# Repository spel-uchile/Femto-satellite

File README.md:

# README #

Femto-satellite v3.211109

### Description ###

This is a low-cost satellite of less than 100 grams. The goal is to deploy two femto-satellites from a 3U CubeSat to validate a localization system based on TDOA and AOA.

### Current features ###

 * GPS localization
 * S band communication
 * 32-bit ARM Cortex M0+ microcontroller
 * Magnetometer PNI RM3100
 * Data logger using a microSD card
 
### To do ###

 * Update the software for the new hardware version
 * Program a low-power mode

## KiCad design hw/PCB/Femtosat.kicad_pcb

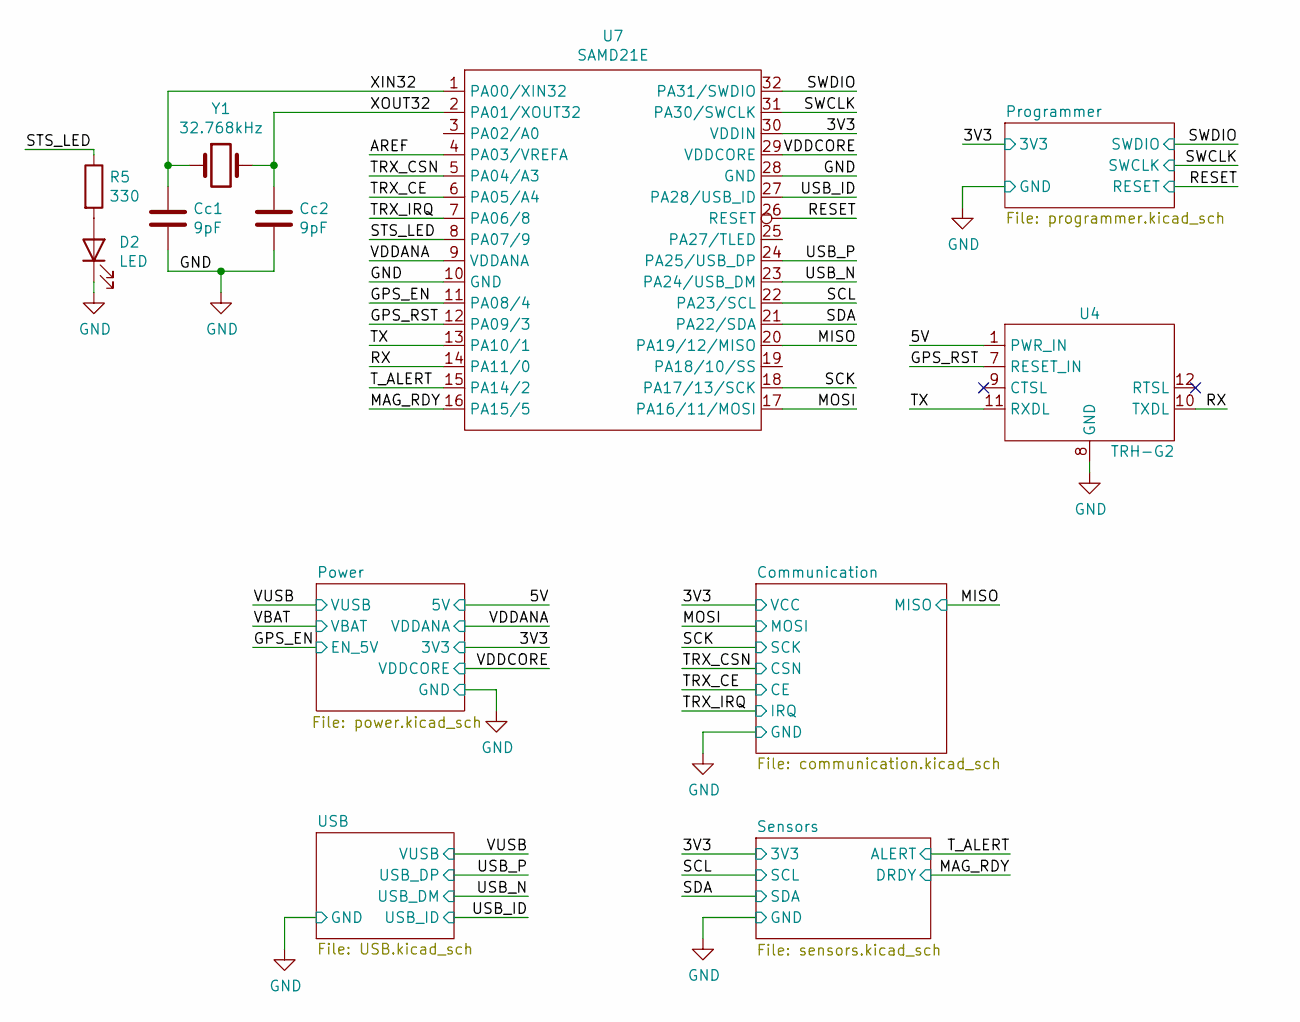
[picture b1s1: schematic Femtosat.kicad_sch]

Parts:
Cc1, Cc2: 9pF; C_0603_1608Metric_Pad1.05x0.95mm_HandSolder
D2: LED; LED_0805_2012Metric_Pad1.15x1.40mm_HandSolder
R5: 330; R_0603_1608Metric_Pad1.05x0.95mm_HandSolder
U4: TRH-G2; TRH-G2_extended
U7: SAMD21E; TQFP-32_7x7mm_P0.8mm
Y1: 32.768kHz; Crystal_SMD_EuroQuartz_EQ161-2Pin_3.2x1.5mm_HandSoldering

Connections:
+3V3: U7.30 (VDDIN); also elsewhere on the board
/5V: U4.1 (PWR_IN), U4.2 (PWR_IN); also elsewhere on the board
/AREF: U7.4 (PA03/VREFA)
/GPS_EN: U7.11 (PA08/4); also elsewhere on the board
/GPS_RST: U4.7 (RESET_IN), U7.12 (PA09/3)
/MAG_RDY: U7.16 (PA15/5); also elsewhere on the board
/MISO: U7.20 (PA19/12/MISO); also elsewhere on the board
/MOSI: U7.17 (PA16/11/MOSI); also elsewhere on the board
/RESET: U7.26 (RESET); also elsewhere on the board
/RX: U4.10 (TXDL), U7.14 (PA11/0)
/SCK: U7.18 (PA17/13/SCK); also elsewhere on the board
/SCL: U7.22 (PA23/SCL); also elsewhere on the board
/SDA: U7.21 (PA22/SDA); also elsewhere on the board
/STS_LED: R5.1, U7.8 (PA07/9)
/SWCLK: U7.31 (PA30/SWCLK); also elsewhere on the board
/SWDIO: U7.32 (PA31/SWDIO); also elsewhere on the board
/TRX_CE: U7.6 (PA05/A4); also elsewhere on the board
/TRX_CSN: U7.5 (PA04/A3); also elsewhere on the board
/TRX_IRQ: U7.7 (PA06/8); also elsewhere on the board
/TX: U4.11 (RXDL), U7.13 (PA10/1)
/T_ALERT: U7.15 (PA14/2); also elsewhere on the board
/USB_ID: U7.27 (PA28/USB_ID); also elsewhere on the board
/USB_N: U7.23 (PA24/USB_DM); also elsewhere on the board
/USB_P: U7.24 (PA25/USB_DP); also elsewhere on the board
/VDDANA: U7.9 (VDDANA); also elsewhere on the board
/VDDCORE: U7.29 (VDDCORE); also elsewhere on the board
/XIN32: Cc1.1, U7.1 (PA00/XIN32), Y1.1
/XOUT32: Cc2.1, U7.2 (PA01/XOUT32), Y1.2
GND: Cc1.2, Cc2.2, D2.1 (K), U4.3 (PGND), U4.4 (PGND), U4.5 (-), U4.6 (-), U4.8 (GND), U7.10 (GND), U7.28 (GND); also elsewhere on the board
unnamed: D2.2 (A), R5.2

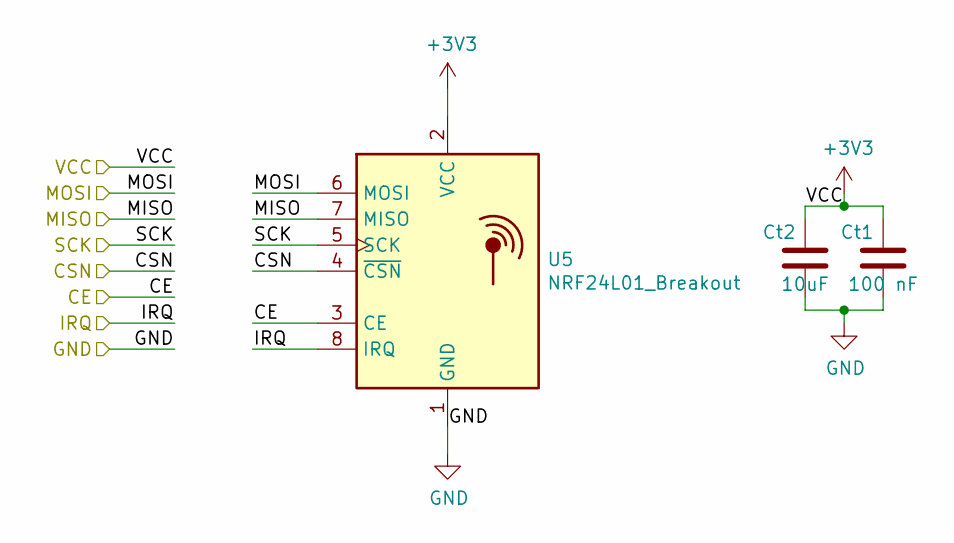
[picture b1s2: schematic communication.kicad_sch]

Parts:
Ct1: 100 nF; C_0603_1608Metric_Pad1.05x0.95mm_HandSolder
Ct2: 10uF; C_0603_1608Metric_Pad1.05x0.95mm_HandSolder
U5: NRF24L01_Breakout; nRF24L01_long

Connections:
+3V3: Ct1.2, Ct2.2, U5.2 (VCC); also elsewhere on the board
/MISO: U5.7 (MISO); also elsewhere on the board
/MOSI: U5.6 (MOSI); also elsewhere on the board
/SCK: U5.5 (SCK); also elsewhere on the board
/TRX_CE: U5.3 (CE); also elsewhere on the board
/TRX_CSN: U5.4 (~CSN); also elsewhere on the board
/TRX_IRQ: U5.8 (IRQ); also elsewhere on the board
GND: Ct1.1, Ct2.1, U5.1 (GND); also elsewhere on the board

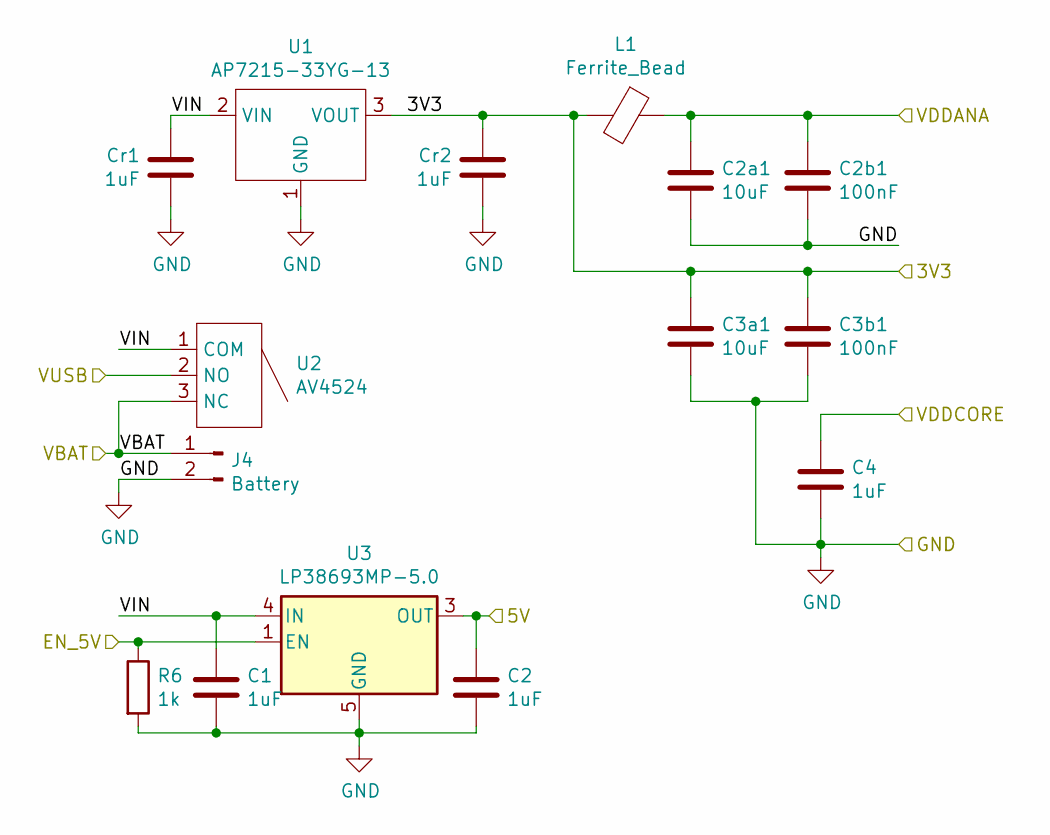
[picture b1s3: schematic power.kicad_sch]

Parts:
C1, C2, C4: 1uF; C_0603_1608Metric_Pad1.05x0.95mm_HandSolder
C2a1, C3a1: 10uF; C_0603_1608Metric_Pad1.05x0.95mm_HandSolder
C2b1, C3b1: 100nF; C_0603_1608Metric_Pad1.05x0.95mm_HandSolder
Cr1, Cr2: 1uF; C_0603_1608Metric_Pad1.05x0.95mm_HandSolder
J4: Battery; JST_PH_S2B-PH-K_1x02_P2.00mm_Horizontal
L1: Ferrite_Bead; L_0805_2012Metric_Pad1.15x1.40mm_HandSolder
R6: 1k; R_0603_1608Metric_Pad1.05x0.95mm_HandSolder
U1: AP7215-33YG-13; SOT-89-3
U2: AV4524
U3: LP38693MP-5.0; SOT-223-5

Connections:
+3V3: C3a1.1, C3b1.1, Cr2.1, L1.2, U1.3 (VOUT); also elsewhere on the board
/5V: C2.1, U3.3 (OUT); also elsewhere on the board
/GPS_EN: R6.1, U3.1 (EN); also elsewhere on the board
/Power/VIN: C1.1, Cr1.1, U1.2 (VIN), U2.1 (COM), U3.4 (IN)
/VBAT: J4.1, U2.3 (NC)
/VDDANA: C2a1.1, C2b1.1, L1.1; also elsewhere on the board
/VDDCORE: C4.1; also elsewhere on the board
/VUSB: U2.2 (NO); also elsewhere on the board
GND: C1.2, C2.2, C2a1.2, C2b1.2, C3a1.2, C3b1.2, C4.2, Cr1.2, Cr2.2, J4.2, R6.2, U1.1 (GND), U3.5 (GND); also elsewhere on the board

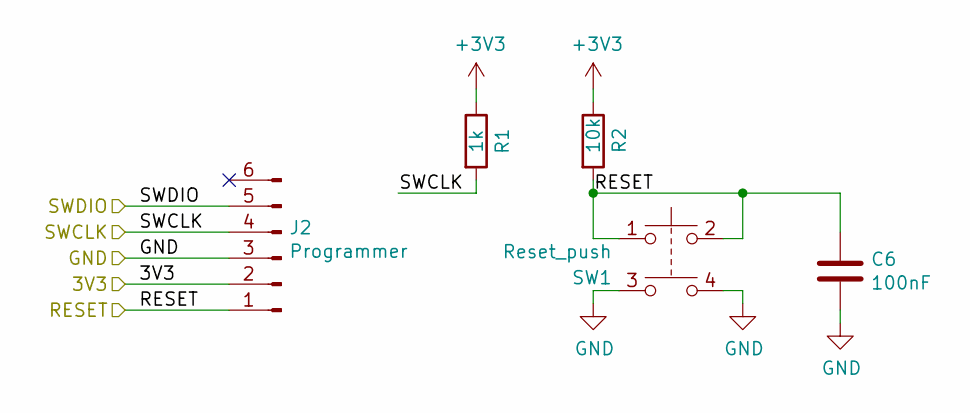
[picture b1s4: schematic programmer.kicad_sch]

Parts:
C6: 100nF; C_0603_1608Metric_Pad1.05x0.95mm_HandSolder
J2: Programmer; Molex_PicoBlade_53261-0671_1x06-1MP_P1.25mm_Horizontal
R1: 1k; R_0603_1608Metric_Pad1.05x0.95mm_HandSolder
R2: 10k; R_0603_1608Metric_Pad1.05x0.95mm_HandSolder
SW1: Reset_push; SW_TH_Tactile_Omron_B3F-10xx

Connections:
+3V3: J2.2, R1.1, R2.1; also elsewhere on the board
/RESET: C6.1, J2.1, R2.2, SW1.1, SW1.2; also elsewhere on the board
/SWCLK: J2.4, R1.2; also elsewhere on the board
/SWDIO: J2.5; also elsewhere on the board
GND: C6.2, J2.3, SW1.3, SW1.4; also elsewhere on the board

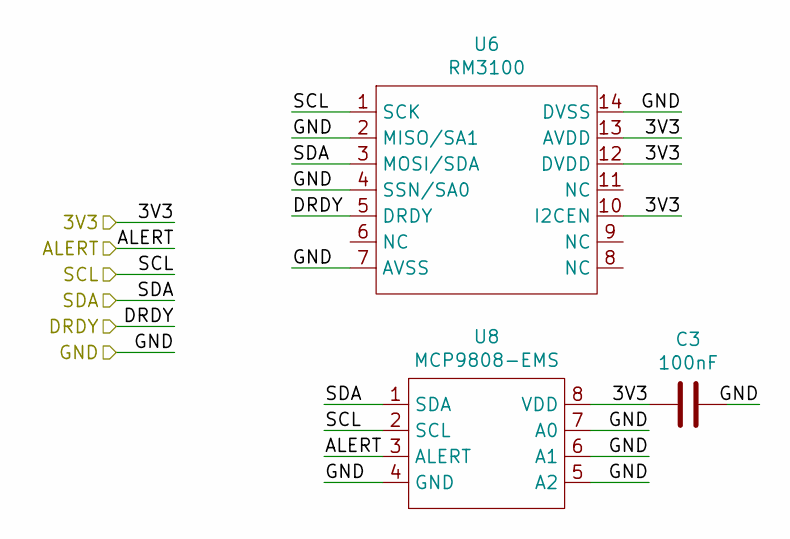
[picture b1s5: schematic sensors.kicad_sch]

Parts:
C3: 100nF; C_0603_1608Metric_Pad1.05x0.95mm_HandSolder
U6: RM3100
U8: MCP9808-EMS; MSOP-8_3x3mm_P0.65mm

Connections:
+3V3: C3.1, U6.10 (I2CEN), U6.12 (DVDD), U6.13 (AVDD), U8.8 (VDD); also elsewhere on the board
/MAG_RDY: U6.5 (DRDY); also elsewhere on the board
/SCL: U6.1 (SCK), U8.2 (SCL); also elsewhere on the board
/SDA: U6.3 (MOSI/SDA), U8.1 (SDA); also elsewhere on the board
/T_ALERT: U8.3 (ALERT); also elsewhere on the board
GND: C3.2, U6.2 (MISO/SA1), U6.4 (SSN/SA0), U6.7 (AVSS), U6.14 (DVSS), U8.4 (GND), U8.5 (A2), U8.6 (A1), U8.7 (A0); also elsewhere on the board

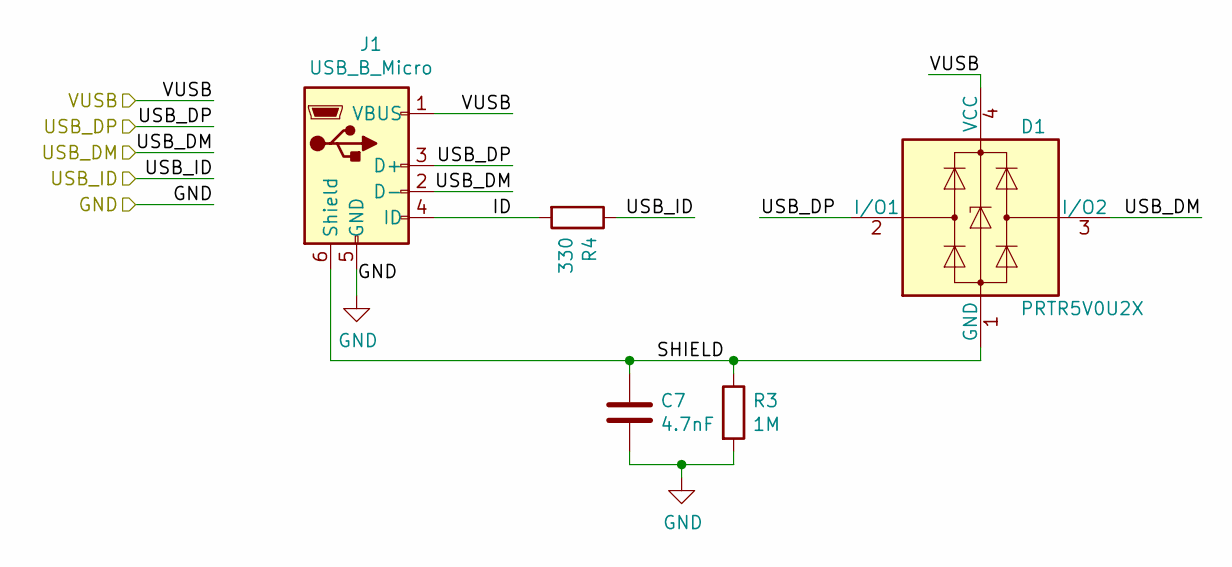
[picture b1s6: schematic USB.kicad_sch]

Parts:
C7: 4.7nF; C_0603_1608Metric_Pad1.05x0.95mm_HandSolder
D1: PRTR5V0U2X; SOT-143
J1: USB_B_Micro; USB_Micro-B_Molex_47346-0001
R3: 1M; R_0603_1608Metric_Pad1.05x0.95mm_HandSolder
R4: 330; R_0603_1608Metric_Pad1.05x0.95mm_HandSolder

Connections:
/USB/ID: J1.4 (ID), R4.2
/USB/SHIELD: C7.1, D1.1 (GND), J1.6 (Shield), R3.1
/USB_ID: R4.1; also elsewhere on the board
/USB_N: D1.3 (I/O2), J1.2 (D-); also elsewhere on the board
/USB_P: D1.2 (I/O1), J1.3 (D+); also elsewhere on the board
/VUSB: D1.4 (VCC), J1.1 (VBUS); also elsewhere on the board
GND: C7.2, J1.5 (GND), R3.2; also elsewhere on the board

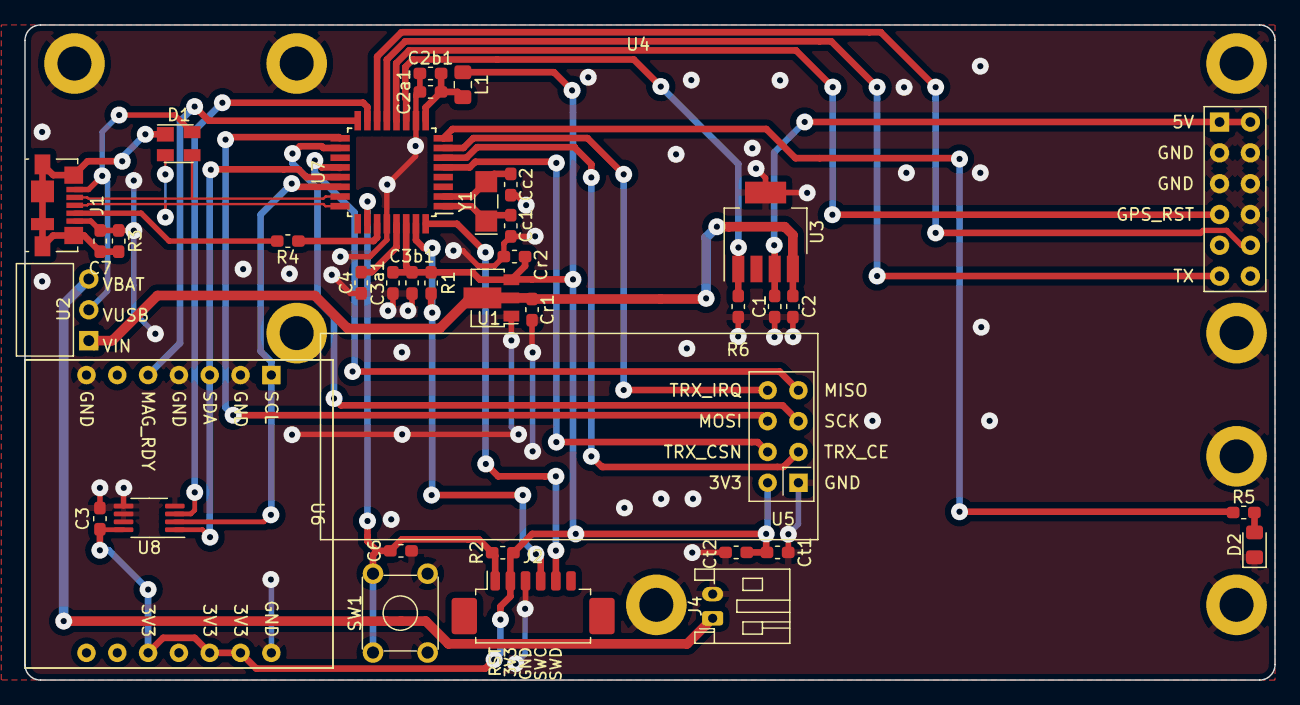
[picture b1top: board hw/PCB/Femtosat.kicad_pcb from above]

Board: 2 copper layers, 103.1 x 54.0 mm, 38 parts (0 on the bottom side), 34 nets.

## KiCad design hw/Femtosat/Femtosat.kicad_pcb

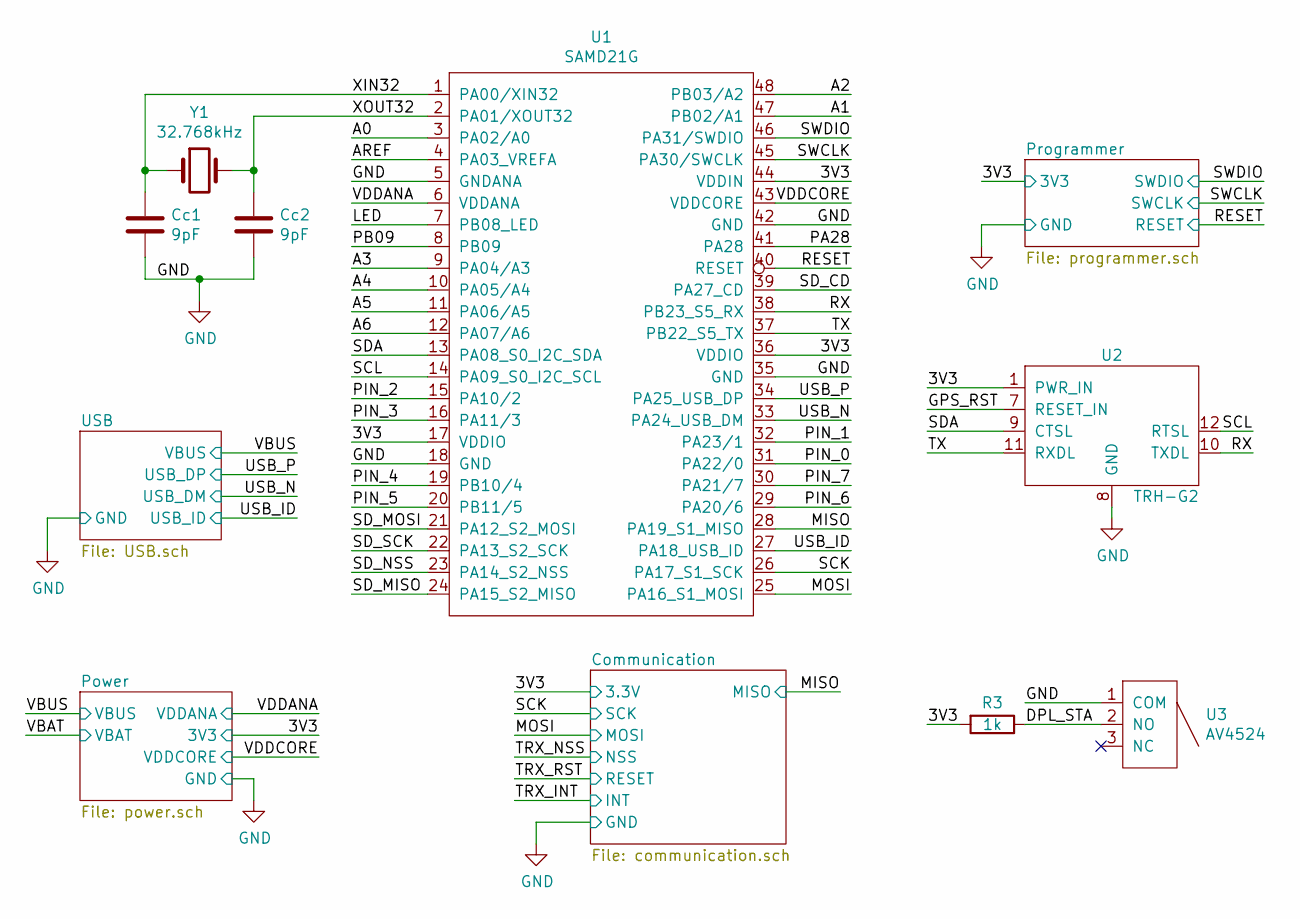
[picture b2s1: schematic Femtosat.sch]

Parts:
Cc1, Cc2: 9pF; C_0603_1608Metric_Pad1.05x0.95mm_HandSolder
R3: 1k; R_0603_1608Metric
U1: SAMD21G; TQFP-48_7x7mm_P0.5mm
U2: TRH-G2
U3: AV4524
Y1: 32.768kHz; Crystal_SMD_EuroQuartz_EQ161-2Pin_3.2x1.5mm_HandSoldering

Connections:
/A0: U1.3 (PA02/A0)
/A1: U1.47 (PB02/A1)
/A2: U1.48 (PB03/A2)
/A3: U1.9 (PA04/A3)
/A4: U1.10 (PA05/A4)
/A5: U1.11 (PA06/A5)
/A6: U1.12 (PA07/A6)
/AREF: U1.4 (PA03_VREFA)
/LED: U1.7 (PB08_LED)
/MISO: U1.28 (PA19_S1_MISO); also elsewhere on the board
/MOSI: U1.25 (PA16_S1_MOSI); also elsewhere on the board
/PA28: U1.41 (PA28)
/PB09: U1.8 (PB09)
/PIN_1: U1.32 (PA23/1)
/PIN_2: U1.15 (PA10/2)
/PIN_3: U1.16 (PA11/3)
/PIN_4: U1.19 (PB10/4)
/PIN_5: U1.20 (PB11/5)
/Power/REG_USB: R3.1, U3.2 (NO); also elsewhere on the board
/RESET: U1.40 (RESET); also elsewhere on the board
/RX: U1.38 (PB23_S5_RX), U2.10 (TXDL)
/SCK: U1.26 (PA17_S1_SCK); also elsewhere on the board
/SD_CD: U1.39 (PA27_CD)
/SD_MISO: U1.24 (PA15_S2_MISO)
/SD_MOSI: U1.21 (PA12_S2_MOSI)
/SD_NSS: U1.23 (PA14_S2_NSS)
/SD_SCK: U1.22 (PA13_S2_SCK)
/SWCLK: U1.45 (PA30/SWCLK); also elsewhere on the board
/SWDIO: U1.46 (PA31/SWDIO); also elsewhere on the board
/TRX_INT: U1.31 (PA22/0); also elsewhere on the board
/TRX_NSS: U1.30 (PA21/7); also elsewhere on the board
/TRX_RST: U1.29 (PA20/6); also elsewhere on the board
/TX: U1.37 (PB22_S5_TX), U2.11 (RXDL)
/USB_ID: U1.27 (PA18_USB_ID); also elsewhere on the board
/USB_N: U1.33 (PA24_USB_DM); also elsewhere on the board
/USB_P: U1.34 (PA25_USB_DP); also elsewhere on the board
/VBAT: U3.3 (NC); also elsewhere on the board
/VDDANA: U1.6 (VDDANA); also elsewhere on the board
/VDDCORE: U1.43 (VDDCORE); also elsewhere on the board
/XIN32: Cc1.1, U1.1 (PA00/XIN32), Y1.1
/XOUT32: Cc2.1, U1.2 (PA01/XOUT32), Y1.2

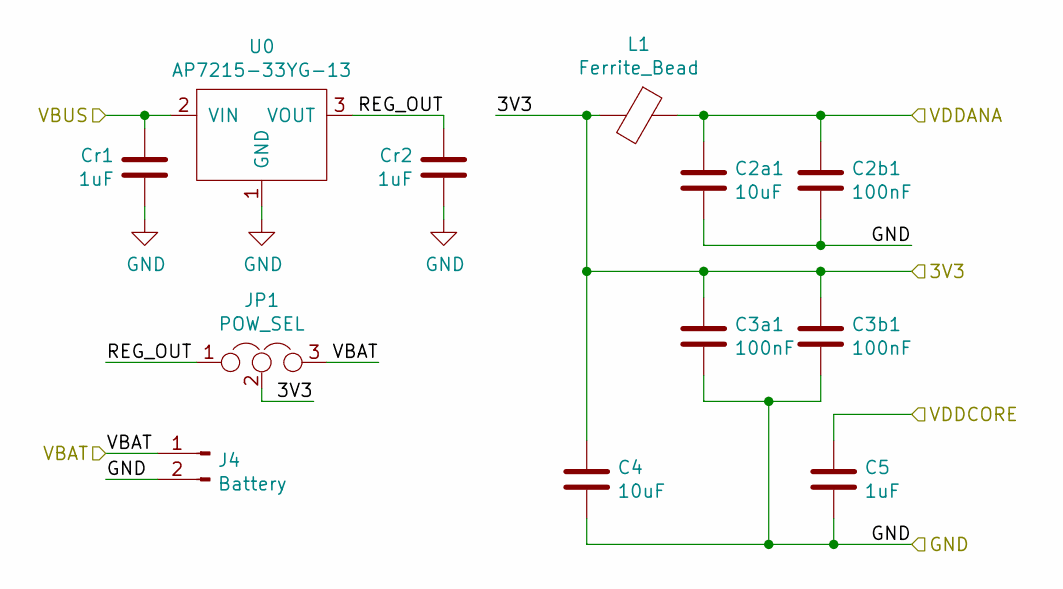
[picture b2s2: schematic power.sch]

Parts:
C2a1, C4: 10uF; C_0603_1608Metric_Pad1.05x0.95mm_HandSolder
C2b1, C3a1, C3b1: 100nF; C_0603_1608Metric_Pad1.05x0.95mm_HandSolder
C5: 1uF; C_0603_1608Metric_Pad1.05x0.95mm_HandSolder
Cr1, Cr2: 1uF; C_0603_1608Metric_Pad1.05x0.95mm_HandSolder
J4: Battery; JST_PH_S2B-PH-K_1x02_P2.00mm_Horizontal
JP1: POW_SEL; PinHeader_1x03_P2.54mm_Vertical
L1: Ferrite_Bead; L_0805_2012Metric_Pad1.15x1.40mm_HandSolder
U0: AP7215-33YG-13; SOT-89-3_Handsoldering

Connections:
/Power/REG_USB: Cr2.1, JP1.1, U0.3 (VOUT); also elsewhere on the board
/VBAT: J4.1, JP1.3; also elsewhere on the board
/VBUS: Cr1.1, U0.2 (VIN); also elsewhere on the board
/VDDANA: C2a1.1, C2b1.1, L1.1; also elsewhere on the board
/VDDCORE: C5.1; also elsewhere on the board

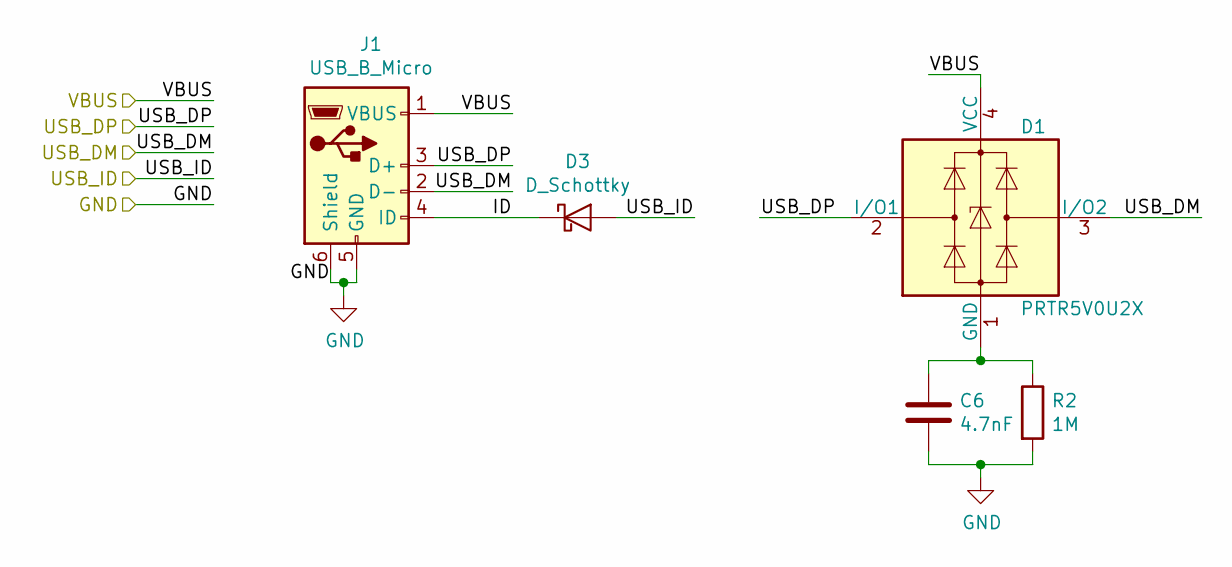
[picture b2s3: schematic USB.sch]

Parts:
C6: 4.7nF; C_0603_1608Metric_Pad1.05x0.95mm_HandSolder
D1: PRTR5V0U2X; SOT-143_Handsoldering
D3: D_Schottky; D_SOD-523
J1: USB_B_Micro; USB_Micro-B_Molex_47346-0001
R2: 1M; R_0603_1608Metric

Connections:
/USB/ID: D3.1 (K), J1.4 (ID)
/USB_ID: D3.2 (A); also elsewhere on the board
/USB_N: D1.3 (I/O2), J1.2 (D-); also elsewhere on the board
/USB_P: D1.2 (I/O1), J1.3 (D+); also elsewhere on the board
/VBUS: D1.4 (VCC), J1.1 (VBUS); also elsewhere on the board
unnamed: C6.1, D1.1 (GND), R2.1

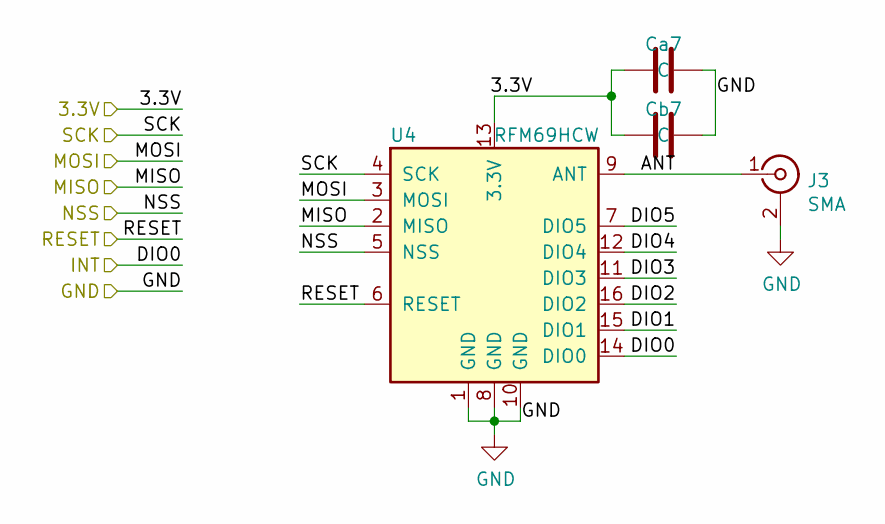
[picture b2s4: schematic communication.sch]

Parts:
Ca7: C; C_0603_1608Metric_Pad1.05x0.95mm_HandSolder
Cb7: C; C_0603_1608Metric_Pad1.05x0.95mm_HandSolder
J3: SMA
U4: RFM69HCW

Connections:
/Communication/ANT: J3.1 (In), U4.9 (ANT)
/Communication/DIO1: U4.15 (DIO1)
/Communication/DIO2: U4.16 (DIO2)
/Communication/DIO3: U4.11 (DIO3)
/Communication/DIO4: U4.12 (DIO4)
/Communication/DIO5: U4.7 (DIO5)
/MISO: U4.2 (MISO); also elsewhere on the board
/MOSI: U4.3 (MOSI); also elsewhere on the board
/SCK: U4.4 (SCK); also elsewhere on the board
/TRX_INT: U4.14 (DIO0); also elsewhere on the board
/TRX_NSS: U4.5 (NSS); also elsewhere on the board
/TRX_RST: U4.6 (RESET); also elsewhere on the board

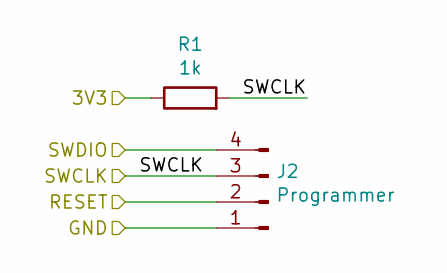
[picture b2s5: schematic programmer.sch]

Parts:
J2: Programmer
R1: 1k

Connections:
/RESET: J2.2; also elsewhere on the board
/SWCLK: J2.3, R1.2; also elsewhere on the board
/SWDIO: J2.4; also elsewhere on the board

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
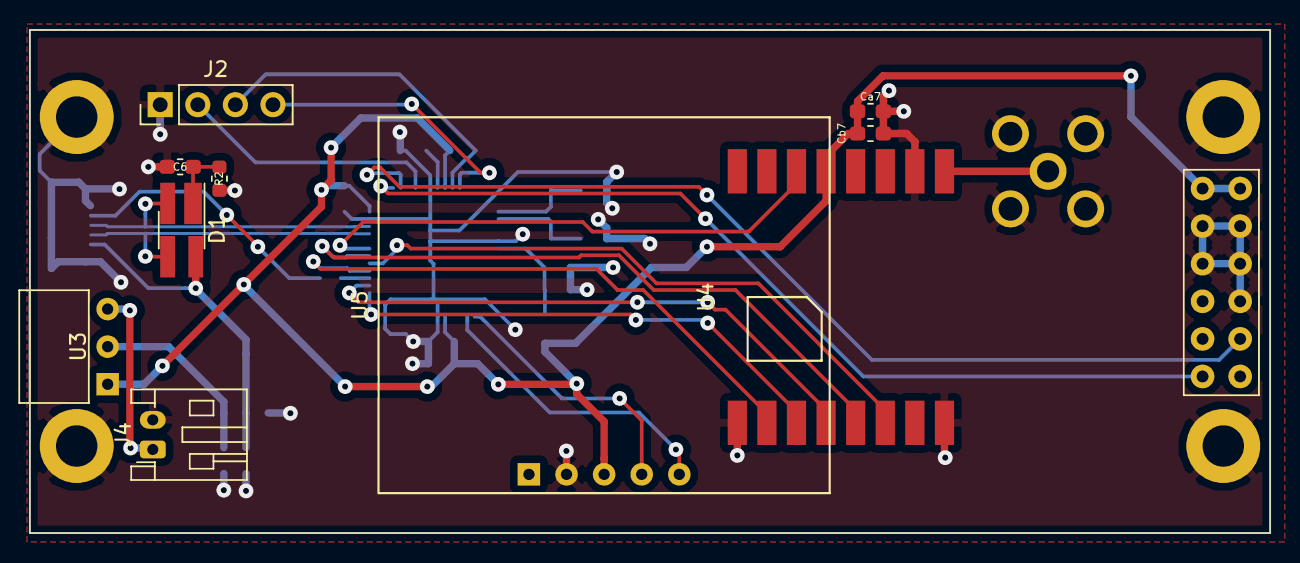
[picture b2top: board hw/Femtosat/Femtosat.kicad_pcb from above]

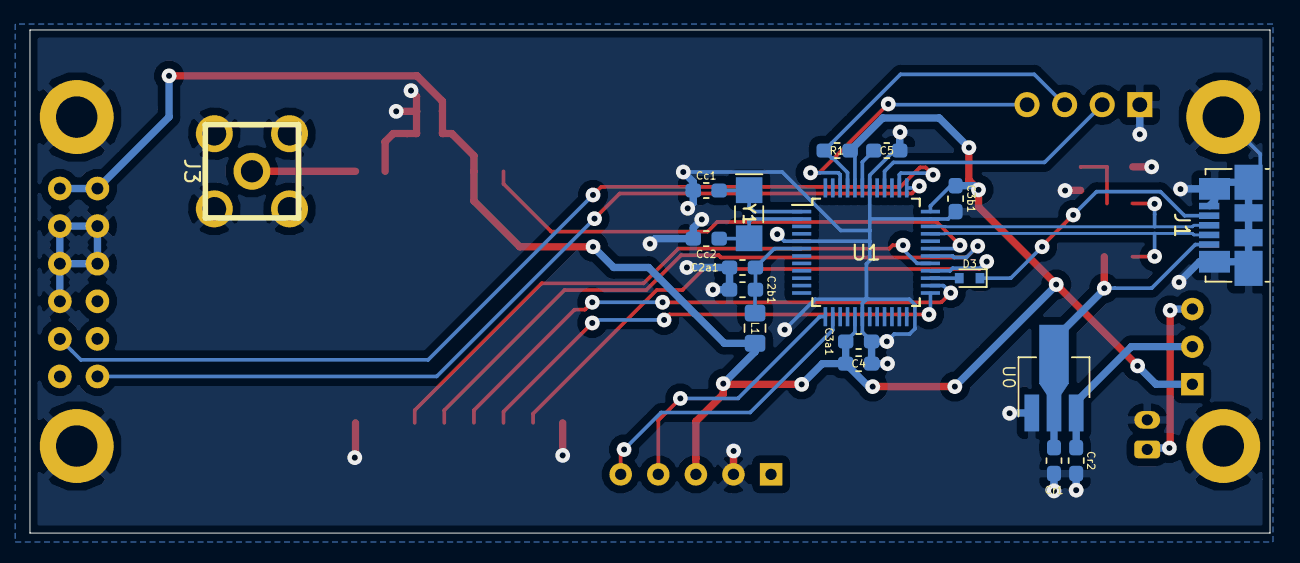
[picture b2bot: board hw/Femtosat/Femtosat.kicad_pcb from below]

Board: 2 copper layers, 83.8 x 34.0 mm, 29 parts (18 on the bottom side), 28 nets.

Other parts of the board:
U5: XA1110; XA1110_I2C

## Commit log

2018-10-19 Added src folder with radio and gps libraries. Also added the main program for the femto-satellite and the pins definitions.
2018-10-22 Improved the project's description.
2018-10-22 Minor changes in comments and indentation.
2018-10-22 Create LICENSE
2018-10-25 Added schematic of the femto-satellite's PCB.
2018-10-25 Added library for certain components. Symbols and footprints were associated.
2018-10-30 Added PCB template with the shape of the TRH-G2 GPS.
2018-10-30 Added capacitors for the communication system.
2018-10-31 Checking for the component's placement on the board.
2018-11-15 Added the Arduino library that contains the pinout of the SAMD21 microcontroller.
2018-11-15 Fixed the error in which the GPS symbol was not found, because its library was in another repository.
2018-11-15 Added library for the power regulator.
2018-11-15 Changed the XA1110 GPS footprint's first pin to a rectangular shape.
2018-11-22 Inscreased the size of the mechanical holes and their pads. Fixed an error in the position of the pins.
2018-11-22 Fixed pads' position error and updated the PCB.
2018-11-22 Deleted the GPS device (moved to another PCB). Added the deploy-sensor (an interrupter). Moved the programmer to its own hierarchical sheet.
2018-11-22 Associated the new symbols to their respective footprints.
2018-11-23 Minor changes.
2018-11-27 Routed all tracks.
2018-11-28 Fixed error in which the GPS was in the top layer instead of the bottom layer. Version 1 released. Changed PCB's folder name to PCB.
2018-11-28 Exported CAD model of the femto-satellite's PCB.
2018-11-28 Minor changes
2018-11-28 Generated gerber files.
2018-11-28 Added more labels in the Silk layer.
2018-11-28 Created new gerber files.
2018-11-28 Exported new CAD design.
2018-12-14 Changed Serial to SerialUSB.
2019-04-29 Specified the capacitance of the transceiver's capacitors. Updated the path of the library for the RFM69HCW.
2019-07-03 Added a footprint library for a micro SD card. Updated the schematic. Replaced the SAMD21G with the SAMD21E (32 pin variant). Added a data logger and a reset button.
2019-07-04 Added pullup resistor to the chip-select pin of the uSD card slot.
2019-07-04 Started the new design of the PCB's layout.
2019-07-05 Replaced a 100nF capacitor with a 10uF capacitor. Worked on PCB preliminary layout.
2019-07-05 Ended preliminary design phase.
2019-07-09 Final revision check. Generated the Gerber files.
2019-07-09 Generated a new CAD file for the 2.0 version.
2019-07-12 Reploted the Gerber files.
2019-07-12 Generated a new CAD file for the femto-satellite v2.0.
2019-07-18 Changed the pin order of the pin header to connect the femto-satellite to the GPS TRH-G2. Now this connector has a battery voltage input for a future EPS board.
2019-07-19 Increased the size of the pad and the drill of the interrupter.
2019-10-18 Added library to handle the femto-satellite's main function.
2019-10-18 Added the command's definitions.
2019-10-18 Changed the way some methods work. Added the available method.
2019-10-18 Changed the definition of the pins.
2019-10-18 Changed the GPS structure.
2019-10-18 Now the femto-satellite follows a logic similar to the FOD.
2021-10-25 New design of the femto-satellite. Deleted UHF transceiver and added another one in S band. Changed the magnetometer. Added more space.
2021-10-25 New CAD file.
2021-10-26 Added the SPEL logo to a library.
2021-10-26 Added a logo to the PCB.
2021-10-26 Generated new Gerber files.
2021-10-26 Generated a new CAD file.
2021-10-26 Updated the README file with some new information.
2021-11-09 Modified the library to support the NRF24L01+ transceiver, and changed some structs for the new beacon.
2022-01-13 Updated the source code for the femto-satellite.
2022-01-19 Added temperature sensor.
2022-01-19 Modified the design of the femto-satellite. Now it is smaller an it has a temperature sensor to calibrate the magnetometer.
2022-02-26 Added a temperature sensor, a GPS receiver and improved the software.
2022-02-26 Removed old library.
2022-02-28 Improved the way the data is stored.
2022-02-28 Updated the frequency.
2022-03-12 Latest version of the femto-satellite.
